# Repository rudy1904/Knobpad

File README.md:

# Knob — panda MIDI keypad

Panda-shaped USB-MIDI controller for Hack Club Half Life (Tier 1): 8 Kailh Choc V1 keys, EC11 encoder, rotary pot, WS2812B underglow, LOLIN S3 Mini (ESP32-S3).

## Status

| Phase | State |
| --- | --- |
| 1. Prep — parts, pinout, footprints | done → `docs/phase1-prep.md` |
| 2. Schematic | done, in review → `docs/phase2-4.md` (ERC 0/0) |
| 3. Footprints + pin check | done, in review → `docs/phase2-4.md` |
| 4. Panda outline | done, in review → `docs/phase2-4.md` (96 × 94 mm, DRC 0) |
| 5. Placement | not started |
| 6. Routing | not started |
| 7. Silkscreen art | not started |
| 8. DRC + exports | not started |
| 9. Firmware | not started |
| 10. Repo + submit | not started |

## Layout

```
hardware/        KiCad 10 project — open hardware/knob.kicad_pro
hardware/lib/    project-local footprints/symbols (Choc V1, S3 Mini)
firmware/        CircuitPython (Phase 9)
docs/            phase notes, parts draft, schematic PDF, images
reports/         ERC / DRC reports
```

`BOM.md` and `JOURNAL.md` are generated by Half Life on sync — don't hand-edit them.

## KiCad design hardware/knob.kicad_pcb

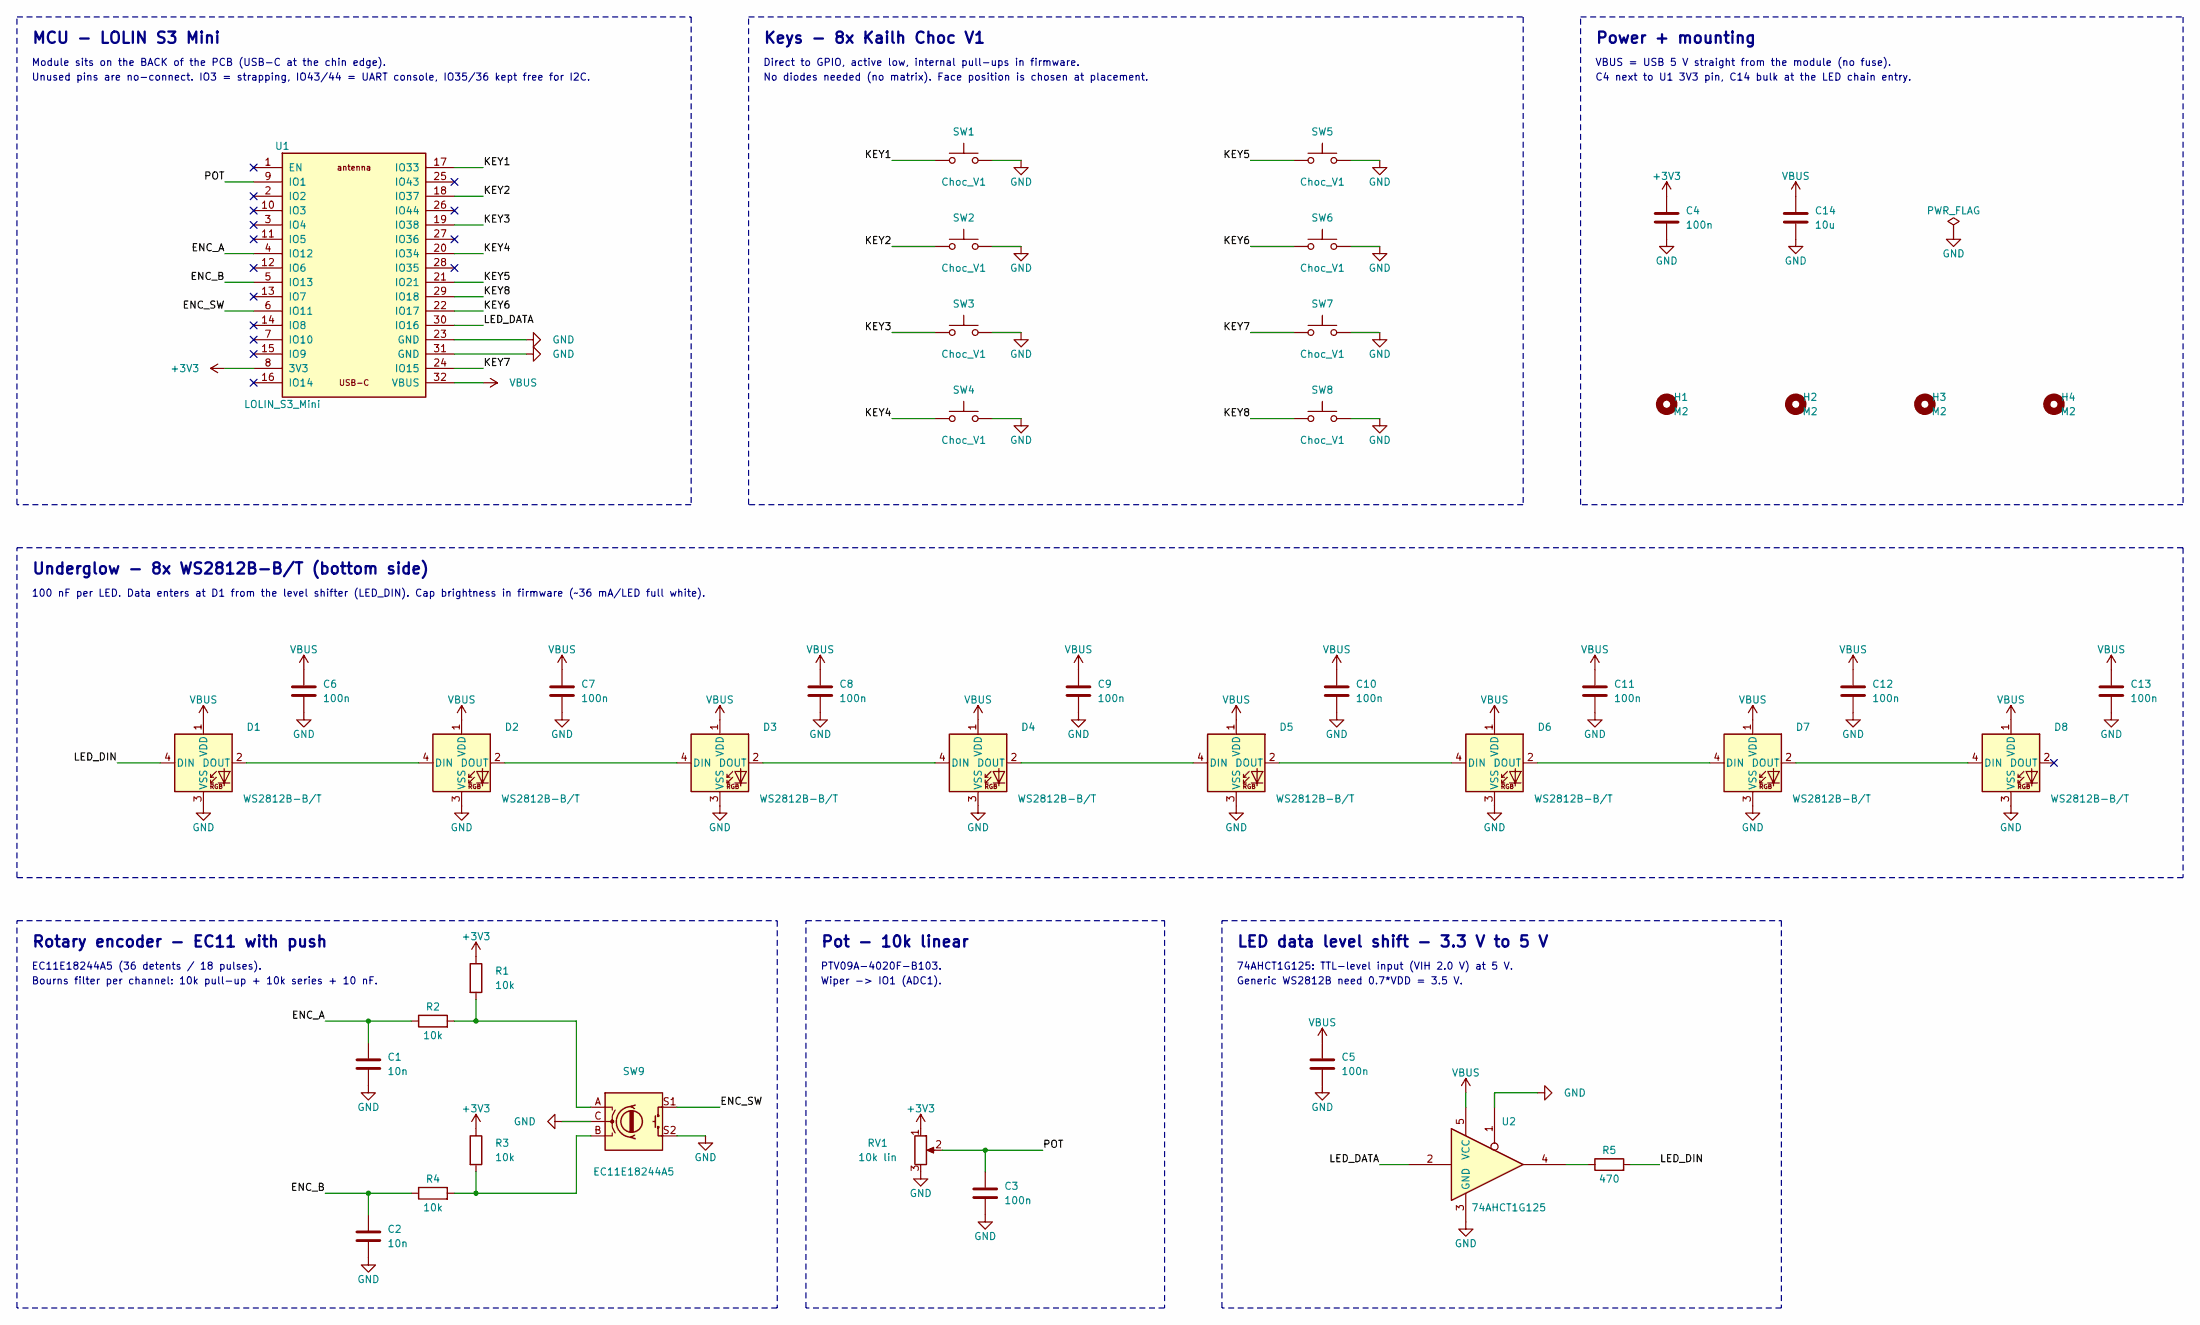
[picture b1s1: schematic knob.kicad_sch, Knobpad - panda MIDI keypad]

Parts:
C1, C2: 10n; C_0805_2012Metric; MPN CC0805KRX7R9BB103; LCSC C83170
C3, C4, C5, C6, C7, C8, C9, C10, C11, C12, C13: 100n; C_0805_2012Metric; MPN CC0805KRX7R9BB104; LCSC C49678
C14: 10u; C_0805_2012Metric; MPN CL21A106KAYNNNE; LCSC C15850
D1, D2, D3, D4, D5, D6, D7, D8: WS2812B-B/T; LED_WS2812B_PLCC4_5.0x5.0mm_P3.2mm; MPN WS2812B-B/T; LCSC C2761795
H1, H2, H3, H4: M2; MountingHole_2.2mm_M2
R1, R2, R3, R4: 10k; R_0805_2012Metric; MPN 0805W8F1002T5E; LCSC C17414
R5: 470; R_0805_2012Metric; MPN 0805W8F4700T5E; LCSC C17710
RV1: 10k lin; Potentiometer_Bourns_PTV09A-1_Single_Vertical; MPN PTV09A-4020F-B103; LCSC C5848782
SW1, SW2, SW3, SW4, SW5, SW6, SW7, SW8: Choc_V1; SW_Kailh_Choc_V1_1.00u; MPN Kailh CPG1350 (Choc V1)
SW9: EC11E18244A5; RotaryEncoder_Alps_EC11E-Switch_Vertical_H20mm; MPN EC11E18244A5; LCSC C255515
U1: LOLIN_S3_Mini; MPN LOLIN S3 Mini v1.0.0
U2: 74AHCT1G125; SOT-23-5; MPN SN74AHCT1G125DBVR; LCSC C7484

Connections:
+3V3: C4.1, R1.1, R3.1, RV1.1, U1.8 (3V3)
/ENC_A: C1.1, R2.1, U1.4 (IO12)
/ENC_B: C2.1, R4.1, U1.5 (IO13)
/ENC_SW: SW9.S1, U1.6 (IO11)
/KEY1: SW1.1, U1.17 (IO33)
/KEY2: SW2.1, U1.18 (IO37)
/KEY3: SW3.1, U1.19 (IO38)
/KEY4: SW4.1, U1.20 (IO34)
/KEY5: SW5.1, U1.21 (IO21)
/KEY6: SW6.1, U1.22 (IO17)
/KEY7: SW7.1, U1.24 (IO15)
/KEY8: SW8.1, U1.29 (IO18)
/LED_DATA: U1.30 (IO16), U2.2
/LED_DIN: D1.4 (DIN), R5.2
/POT: C3.1, RV1.2, U1.9 (IO1)
GND: C1.2, C2.2, C3.2, C4.2, C5.2, C6.2, C7.2, C8.2, C9.2, C10.2, C11.2, C12.2, C13.2, C14.2, D1.3 (VSS), D2.3 (VSS), D3.3 (VSS), D4.3 (VSS), D5.3 (VSS), D6.3 (VSS), D7.3 (VSS), D8.3 (VSS), RV1.3, SW1.2, SW2.2, SW3.2, SW4.2, SW5.2, SW6.2, SW7.2, SW8.2, SW9.C, SW9.S2, U1.23 (GND), U1.31 (GND), U2.1, U2.3 (GND)
unnamed: D1.2 (DOUT), D2.4 (DIN)
unnamed: D2.2 (DOUT), D3.4 (DIN)
unnamed: D3.2 (DOUT), D4.4 (DIN)
unnamed: D4.2 (DOUT), D5.4 (DIN)
unnamed: D5.2 (DOUT), D6.4 (DIN)
unnamed: D6.2 (DOUT), D7.4 (DIN)
unnamed: D7.2 (DOUT), D8.4 (DIN)
unnamed: R1.2, R2.2, SW9.A
unnamed: R3.2, R4.2, SW9.B
unnamed: R5.1, U2.4
VBUS: C5.1, C6.1, C7.1, C8.1, C9.1, C10.1, C11.1, C12.1, C13.1, C14.1, D1.1 (VDD), D2.1 (VDD), D3.1 (VDD), D4.1 (VDD), D5.1 (VDD), D6.1 (VDD), D7.1 (VDD), D8.1 (VDD), U1.32 (VBUS), U2.5 (VCC)

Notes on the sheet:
Rotary encoder - EC11 with push
No diodes needed (no matrix). Face position is chosen at placement.
C4 next to U1 3V3 pin, C14 bulk at the LED chain entry.
LED data level shift - 3.3 V to 5 V
PTV09A-4020F-B103.
Generic WS2812B need 0.7*VDD = 3.5 V.
Module sits on the BACK of the PCB (USB-C at the chin edge).
Pot - 10k linear
Keys - 8x Kailh Choc V1
Underglow - 8x WS2812B-B/T (bottom side)
Wiper -> IO1 (ADC1).
Direct to GPIO, active low, internal pull-ups in firmware.
Power + mounting
MCU - LOLIN S3 Mini
Unused pins are no-connect. IO3 = strapping, IO43/44 = UART console, IO35/36 kept free for I2C.
Bourns filter per channel: 10k pull-up + 10k series + 10 nF.
EC11E18244A5 (36 detents / 18 pulses).
74AHCT1G125: TTL-level input (VIH 2.0 V) at 5 V.
100 nF per LED. Data enters at D1 from the level shifter (LED_DIN). Cap brightness in firmware (~36 mA/LED full white).
VBUS = USB 5 V straight from the module (no fuse).

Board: 2 copper layers, 43 parts (9 on the bottom side), 27 nets, no tracks yet.

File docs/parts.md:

# Knob (panda MIDI keypad) — parts draft

Prices/stock checked on LCSC on 2026-10-22. "est." = NOT checked, placeholder only.
This is the working list. Half Life generates and overwrites `BOM.md` on sync (same as Hushlog), so enter the final list on the platform; don't hand-edit `BOM.md`.

| Ref | Part | MPN | Source | Buy qty | Unit $ | Line $ | Notes |
| --- | --- | --- | --- | --- | --- | --- | --- |
| U1 | LOLIN S3 Mini (ESP32-S3FH4R2) | — | Wemos official store; not on LCSC | 1 | est. 5 | est. 5 | |
| SW1–SW8 | Kailh Choc V1 switch | CPG1350xx (pick feel) | **Not available on LCSC** (all Kailh Choc listings "Not available now") — Kailh store / Indian keyboard shop | 10 (2 spare) | est. 0.6 | est. 6 | |
| — | Choc V1 1u keycaps | — | same as switches | 8 | est. 0.6 | est. 5 | Must be Choc-stem; MX keycaps don't fit V1 |
| SW9 | Encoder + push, 36 det / 18 pulses | EC11E18244A5 | [LCSC C255515](https://www.lcsc.com/product-detail/C255515.html) | 1 | 2.4355 | 2.44 | 284 in stock |
| RV1 | 10k linear pot, 9 mm, shaft up, bushingless, 20 mm flat shaft | PTV09A-4020F-B103 | [LCSC C5848782](https://www.lcsc.com/product-detail/C5848782.html) | 1 | 0.5822 | 0.58 | 200 in stock, other-supplier stock, 5–7 day lead |
| D1–D8 | Addressable RGB LED 5050 | WS2812B-B/T | [LCSC C2761795](https://www.lcsc.com/product-detail/C2761795.html) | 10 (MOQ 5) | 0.1182 | 1.18 | 20,895 in stock; LCSC marks it Discontinued — fine for one build |
| U2 | Buffer, TTL-level input (3.3 V → 5 V data) | SN74AHCT1G125DBVR | [LCSC C7484](https://www.lcsc.com/product-detail/C7484.html) | 5 (MOQ 5) | 0.1011 | 0.51 | Only if decision D1 = yes |
| R1–R4 | 10 kΩ 0805 1% | 0805W8F1002T5E | [LCSC C17414](https://www.lcsc.com/product-detail/C17414.html) | 100 | 0.0034 | 0.34 | Encoder: 2 pull-ups + 2 series |
| R5 | 470 Ω 0805 1% | 0805W8F4700T5E | [LCSC C17710](https://www.lcsc.com/product-detail/C17710.html) | 100 | 0.0049 | 0.49 | LED data series resistor |
| C1–C2 | 10 nF 0805 X7R 50 V | CC0805KRX7R9BB103 | [LCSC C83170](https://www.lcsc.com/product-detail/C83170.html) | 100 | 0.0082 | 0.82 | Encoder filter. (C1710, the usual pick, is out of stock) |
| C3–C13 | 100 nF 0805 X7R 50 V | CC0805KRX7R9BB104 | [LCSC C49678](https://www.lcsc.com/product-detail/C49678.html) | 20 | 0.0206 | 0.41 | 1 per LED (8) + pot + 3V3 + U2 |
| C14 | 10 µF 0805 X5R 25 V | CL21A106KAYNNNE | [LCSC C15850](https://www.lcsc.com/product-detail/C15850.html) | 20 | 0.0429 | 0.86 | Bulk at LED chain (replaces the plan's 1000 µF) |
| — | Knobs for EC11 + PTV09 shafts | — | any | 2 | est. 0.5 | est. 1 | Match the shaft type in each datasheet |
| — | M2 standoffs/feet + screws | — | any | 4 sets | est. 0.25 | est. 1 | Height must clear the module on the back |
| — | PCB 2-layer, ≤100 × 100 mm, 5 pcs | — | JLCPCB | 1 | est. 2–5 | est. 2–5 | + shipping |

**LCSC lines (verified): $7.63** (with U2). Estimated other lines: ~$20–23. **Total ≈ $28–31 before shipping/customs** — right at the $30 target, so the switch/keycap/module prices decide it. LCSC shipping to India is not included; Half Life's site says customs aren't covered.
